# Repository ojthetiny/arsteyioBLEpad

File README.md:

# arsteyioBLEpad

an nRF52 powered macropad built to utilize the "ARTSEYIO" layout by whydobearsxplod.
featuring a thumb key on a breakout board with the usb connector to make the layout actually usable

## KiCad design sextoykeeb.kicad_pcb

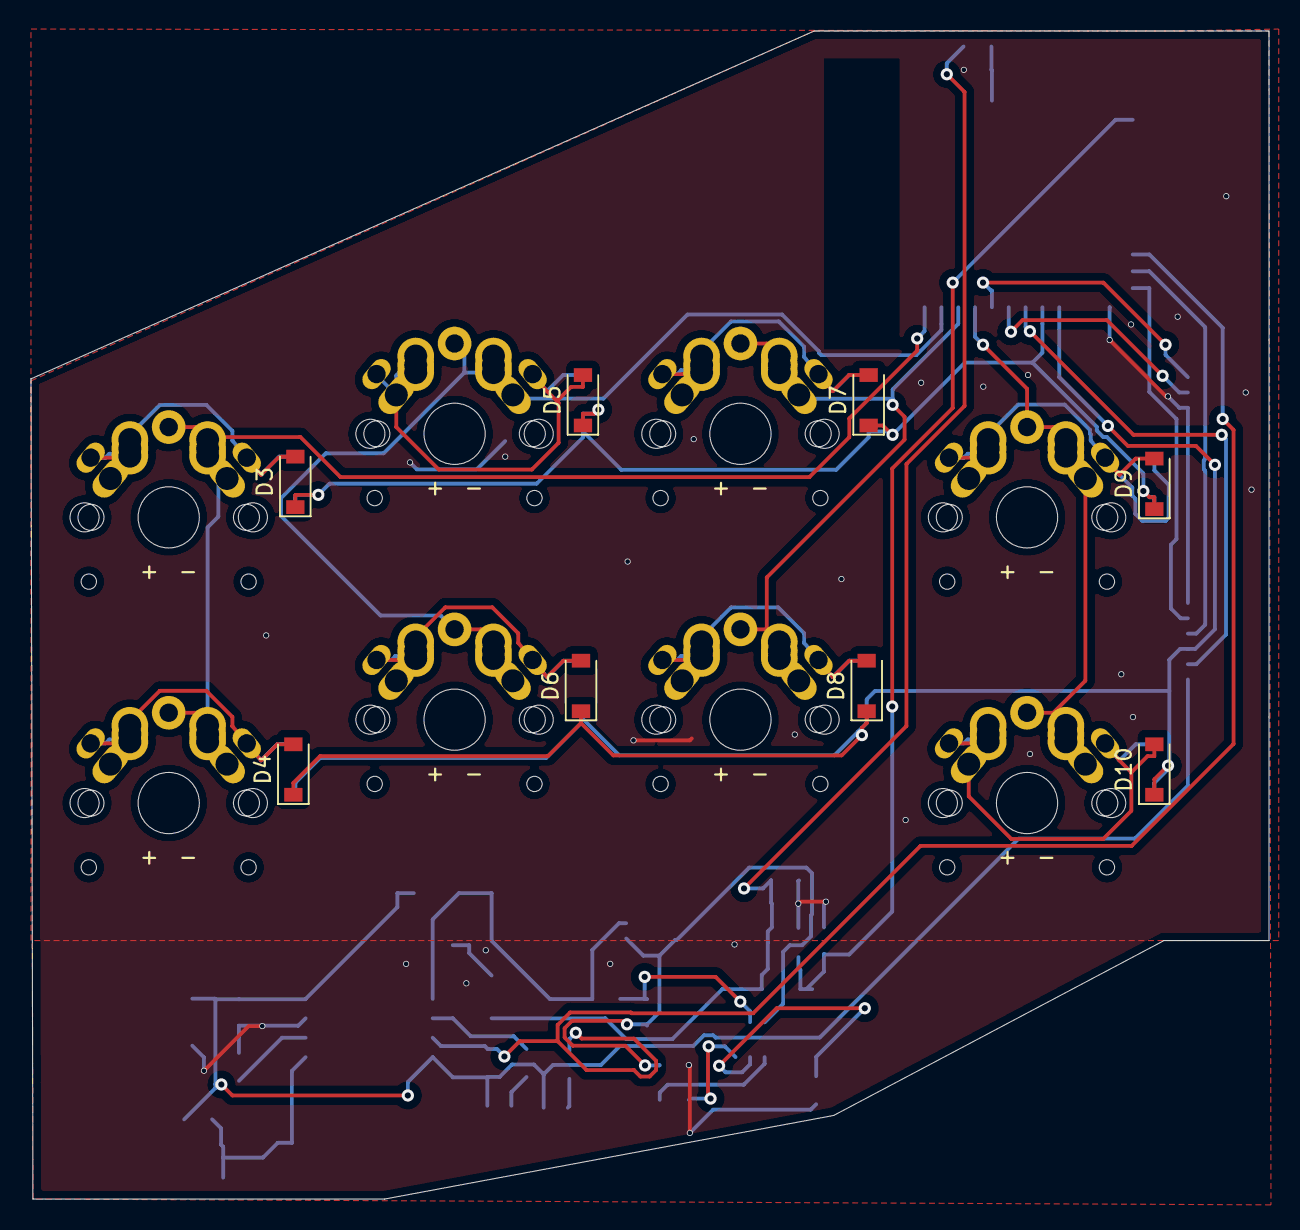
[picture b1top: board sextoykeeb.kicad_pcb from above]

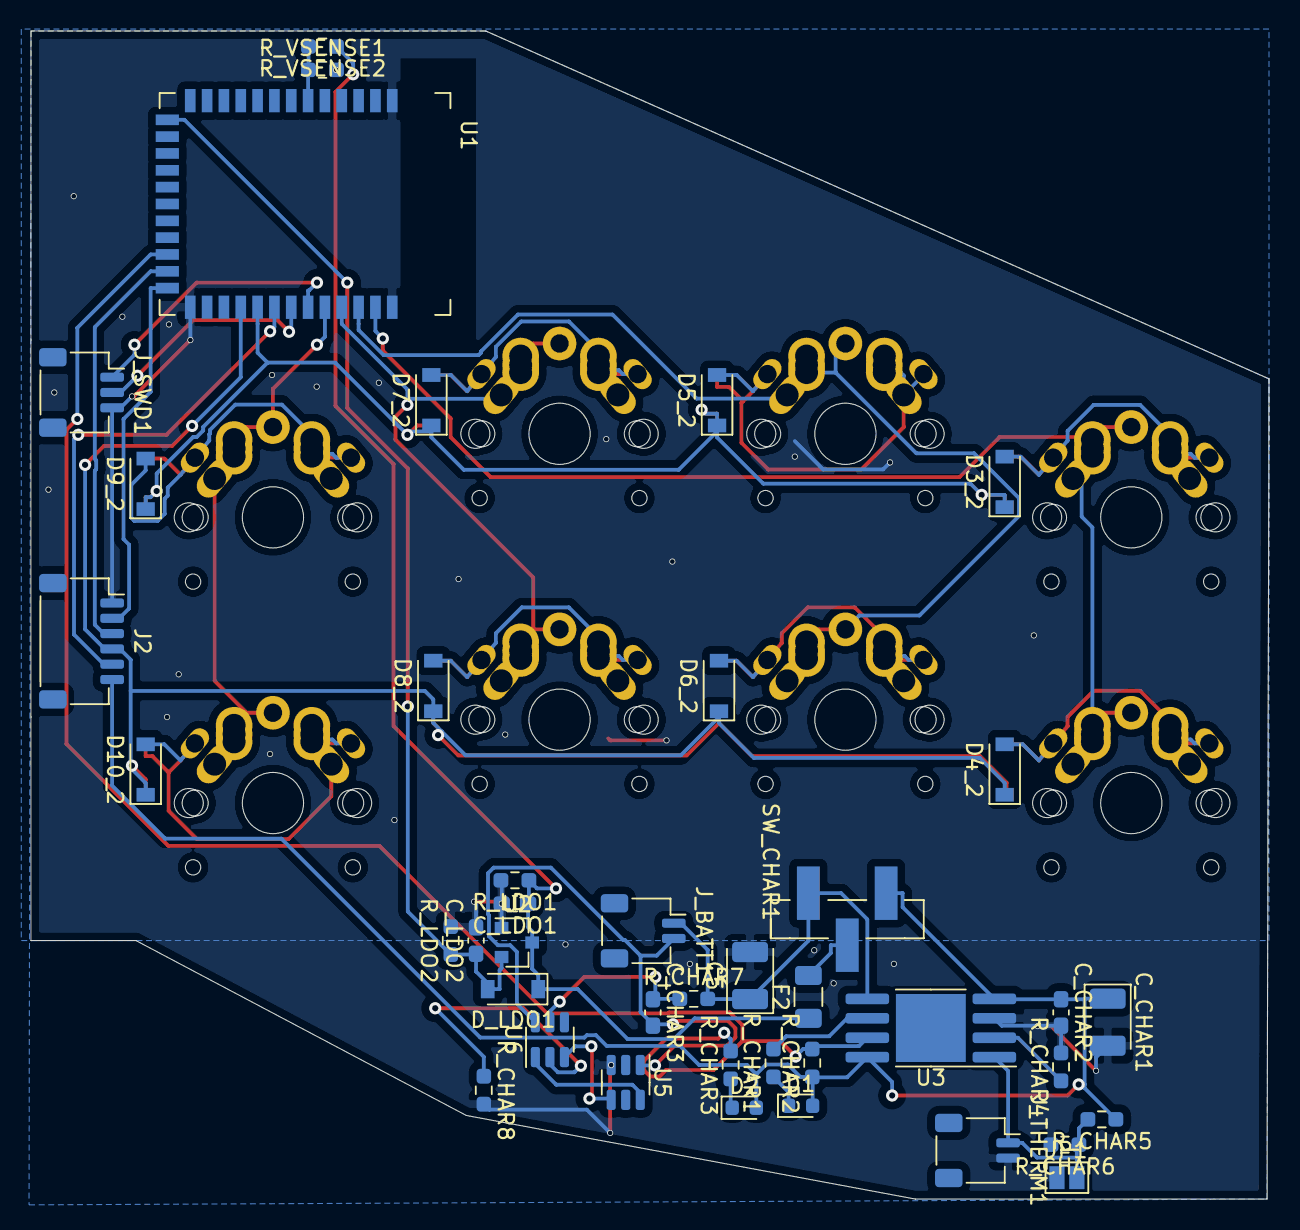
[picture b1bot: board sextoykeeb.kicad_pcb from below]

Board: 2 copper layers, 80.9 x 76.3 mm, 57 parts (41 on the bottom side), 37 nets.

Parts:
C5: C_Polarized_Small; CP_EIA-3528-21_Kemet-B
C_CHAR1: 10u; CP_EIA-3528-21_Kemet-B
C_CHAR2, C_CHAR3: 100n; C_0603_1608Metric_Pad1.08x0.95mm_HandSolder
C_LDO1, C_LDO2: 100n; C_0603_1608Metric_Pad1.08x0.95mm_HandSolder
D1, D2: LED_Small; LED_0603_1608Metric
D3, D3_2, D4, D4_2, D5, D5_2, D6, D6_2, D7, D7_2, D8, D8_2, D9, D9_2, D10, D10_2: D_Small; D_SOD-123
D_LDO1: D_Schottky; D_SOD-123
F2: SCF075-1206R; Fuse_1206_3216Metric
J2: Conn_01x06; JST_SH_SM06B-SRSS-TB_1x06-1MP_P1.00mm_Horizontal
JP1: Jumper_2_Open; SolderJumper-2_P1.3mm_Open_Pad1.0x1.5mm
J_BATT1: Conn_01x02; JST_SH_SM02B-SRSS-TB_1x02-1MP_P1.00mm_Horizontal
J_SWD1: Conn_01x03; JST_SH_SM03B-SRSS-TB_1x03-1MP_P1.00mm_Horizontal
J_THERM1: Conn_01x02; JST_SH_SM02B-SRSS-TB_1x02-1MP_P1.00mm_Horizontal
R_CHAR1, R_CHAR3: 2.7k; R_0603_1608Metric_Pad0.98x0.95mm_HandSolder
R_CHAR2: 10k; R_0603_1608Metric_Pad0.98x0.95mm_HandSolder
R_CHAR4: 1.8k; R_0603_1608Metric_Pad0.98x0.95mm_HandSolder
R_CHAR5: 3.3k; R_0603_1608Metric_Pad0.98x0.95mm_HandSolder
R_CHAR6: 22k; R_0603_1608Metric_Pad0.98x0.95mm_HandSolder
R_CHAR7: 100; R_0603_1608Metric_Pad0.98x0.95mm_HandSolder
R_CHAR8: 1k; R_0603_1608Metric_Pad0.98x0.95mm_HandSolder
R_LDO1, R_LDO2: 100k; R_0603_1608Metric_Pad0.98x0.95mm_HandSolder
R_VSENSE1: 2M; R_0603_1608Metric_Pad0.98x0.95mm_HandSolder
R_VSENSE2: 1.3M; R_0603_1608Metric_Pad0.98x0.95mm_HandSolder
SW1, SW2, SW3, SW4, SW5, SW6, SW7, SW8: SW_Push; MX_ALPS_PG1350_noLed
SW_CHAR1: SW_SPDT; ESP3020
U1: nRF52840_holyiot_18010
U2: MCP1700-3302E_SOT23; SOT-23
U3: TP4056; SOP-8-1EP_4.57x4.57mm_P1.27mm_EP4.57x4.45mm
U5: FS8205; SOT-23-6
U6: DW01A; SOT-23-6

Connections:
+3V3: C_LDO2.1, D_LDO1.2, R_LDO2.1, U1.14, U2.2
+5V: C_LDO1.1, D_LDO1.1, F2.1, R_LDO1.1, R_VSENSE2.1, U2.3
+5VA: C_CHAR1.1, C_CHAR2.1, D1.2, D2.2, J2.6, R_CHAR2.1, R_CHAR5.1, SW_CHAR1.3, U3.4, U3.8
COL0: SW1.2, SW2.2, U1.36
COL1: SW3.2, SW4.2, U1.35
COL2: SW5.2, SW6.2, U1.34
COL3: SW7.2, SW8.2, U1.33
COL4: J2.5, U1.30
D+: J2.2, U1.24
D-: J2.3, U1.23
GND: C5.2, C_CHAR1.2, C_CHAR2.2, C_LDO1.2, C_LDO2.2, J2.1, JP1.1, J_SWD1.3, J_THERM1.2, R_CHAR4.2, R_CHAR6.2, R_CHAR8.2, R_LDO1.2, R_LDO2.2, R_VSENSE1.2, U1.1, U1.25, U1.37, U2.1, U3.3, U5.3
unnamed: C5.1, J_BATT1.1, R_CHAR7.2, SW_CHAR1.1, U3.5
unnamed: C_CHAR3.1, R_CHAR7.1, U6.5
unnamed: C_CHAR3.2, J_BATT1.2, U5.1, U6.6
unnamed: D1.1, R_CHAR1.1
unnamed: D2.1, R_CHAR3.1
unnamed: D3.2, D3_2.2, SW1.1
unnamed: D4.2, D4_2.2, SW2.1
unnamed: D5.2, D5_2.2, SW3.1
unnamed: D6.2, D6_2.2, SW4.1
unnamed: D7.2, D7_2.2, SW5.1
unnamed: D8.2, D8_2.2, SW6.1
unnamed: D9.2, D9_2.2, SW7.1
unnamed: D10.2, D10_2.2, SW8.1
unnamed: JP1.2, J_THERM1.1, R_CHAR5.2, R_CHAR6.1, U3.1
unnamed: J_SWD1.1, U1.32
unnamed: J_SWD1.2, U1.31
unnamed: R_CHAR1.2, U3.6
unnamed: R_CHAR4.1, U3.2
unnamed: R_CHAR8.1, U6.2
unnamed: R_VSENSE1.1, R_VSENSE2.2, U1.6
unnamed: U5.4, U6.3
unnamed: U5.6, U6.1
ROW0: D3.1, D3_2.1, D5.1, D5_2.1, D7.1, D7_2.1, D9.1, D9_2.1, U1.29
ROW1: D4.1, D4_2.1, D6.1, D6_2.1, D8.1, D8_2.1, D10.1, D10_2.1, J2.4, U1.28
VBUS: R_CHAR2.2, R_CHAR3.2, U1.22, U3.7
VOUT: F2.2, SW_CHAR1.2

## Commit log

2020-11-23 finished PCB
2020-11-23 finished pcb for real this time
2020-11-23 Added License
2020-11-24 switched to 'Taylor spacing', moved most of the components, reversible switch footprints
